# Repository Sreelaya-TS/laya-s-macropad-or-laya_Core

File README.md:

# Laya Core – 4-Key OLED Macropad 

**Honestly this was my first hardware project and this would be my 3rd edit I have added a oled that displays a cute pic**
I made this for fun and exposure to design my own pcb overall the project was fun to make and I had my good time figuring out and learning how a keyboard actualy works from yt videos, documentations and github repos etc. and for this project since I knew python already I have used kmk firmware and all the keys r directly connected to mcu 

This project includes a **custom PCB**, **KMK firmware**, and a **3D-printed case**.

---

##PARTS USED

- 4 programmable mechanical keys  
- XIAO RP2040 microcontroller  
- OLED display (I2C, 128×64)  
- KMK (CircuitPython-based) firmware  
- Custom PCB designed in KiCad  
- 3D printed enclosure (Fusion 360)
- 4 × M3 × 10 mm self-tapping screws  

---

## Firmware

- Written using **KMK firmware**
- Supports:
  - Custom keyboard shortcuts i just have added (screenshots, copy, paste, etc.)
  - OLED bitmap display (cute robot graphic)

> Firmware source code is available in this repository.

---

## 📸 Project Images

### 🟢 PCB Layout
<!-- Add your PCB image here -->

---

### 🔵 Schematic
<!-- Add your schematic image here -->

---

### 🟣 Final 3D Model (Fusion 360)
<!-- Add your Fusion 360 render here -->

---

## 🔌 OLED Display

- OLED communicates via **I2C**
- Resolution: **128 × 64**
- Displays a custom bitmap 
---

## 🧩 Bill of Materials (BOM)

---

## 🛠️ Tools Used

- **KiCad** – schematic and PCB design  
- **Fusion 360** – 3D modeling  
- **KMK Firmware** – keyboard firmware  
- **CircuitPython**  
- **Git & GitHub**
---

## 💙 Author

**Sreelaya TS**  
---

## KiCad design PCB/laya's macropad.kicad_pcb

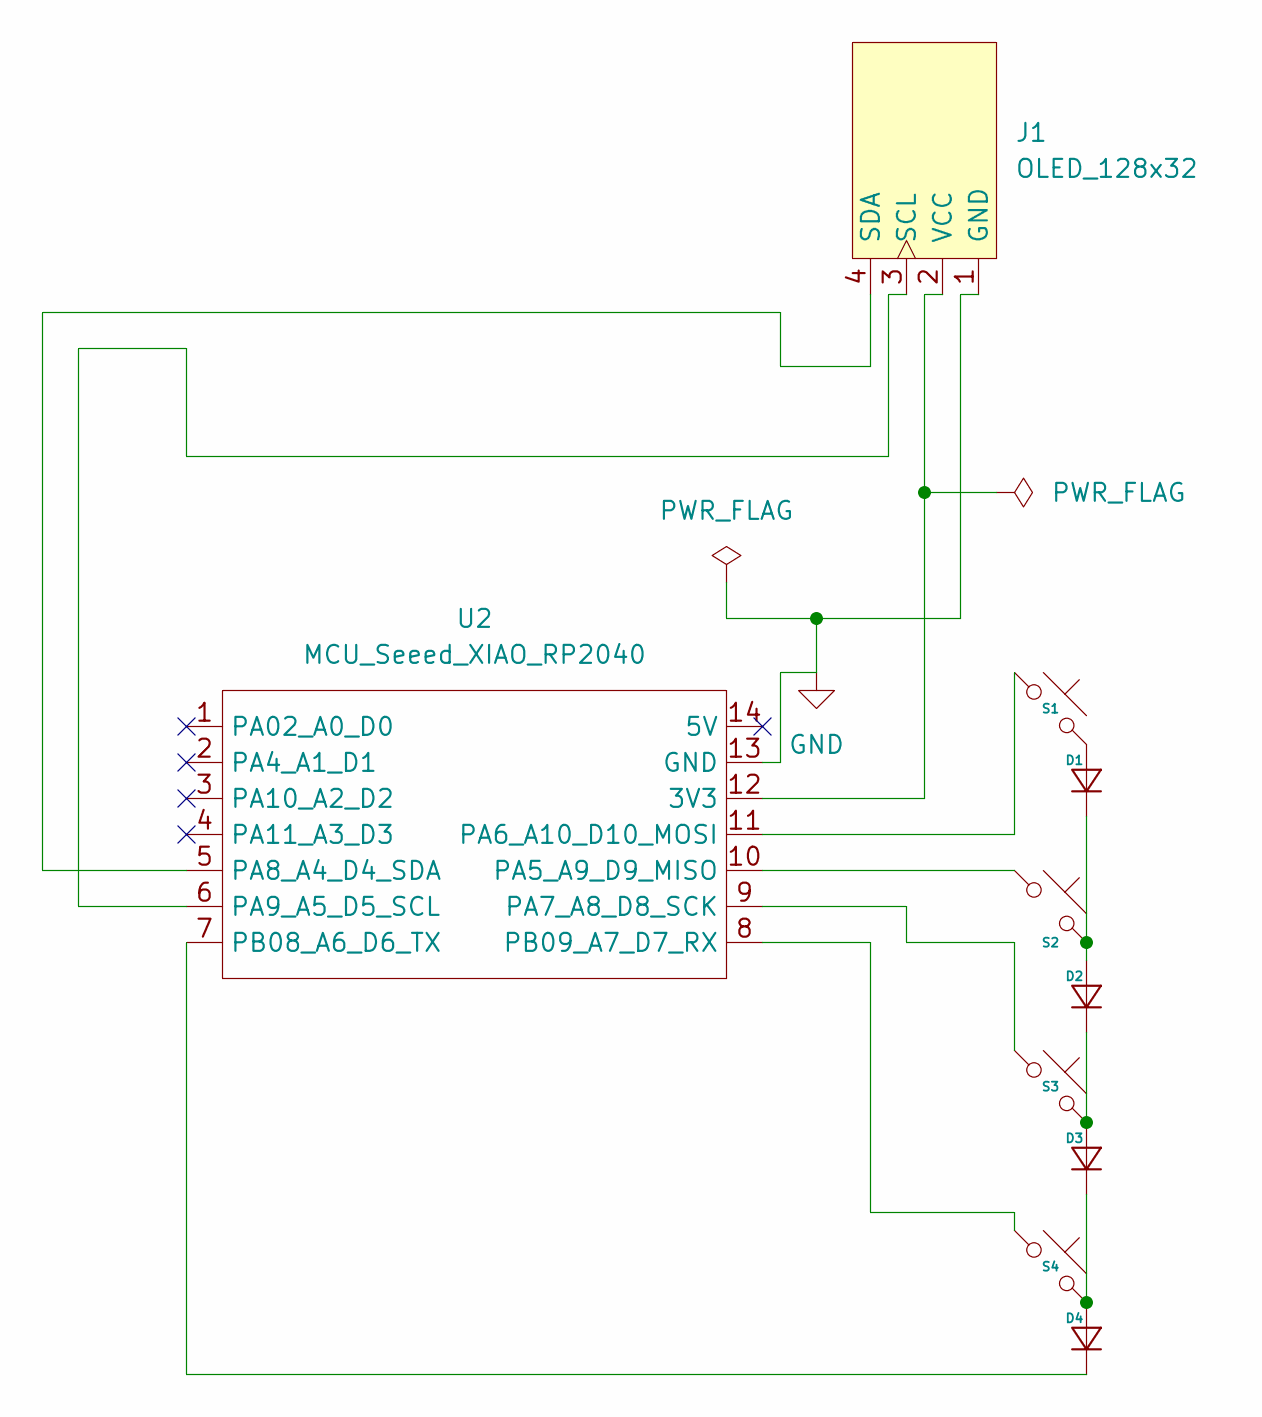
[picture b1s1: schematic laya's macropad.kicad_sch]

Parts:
D1, D2, D3, D4: Diode_DO-35
J1: OLED_128x32
S1, S2, S3, S4: MX_PCB_1.00u
U2: MCU_Seeed_XIAO_RP2040; Seeed_XIAO_RP2040

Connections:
GND: J1.1 (GND), U2.13 (GND)
unnamed: D1.2 (A), S1.2
unnamed: D1.1 (K), D2.2 (A), S2.2
unnamed: D2.1 (K), D3.2 (A), S3.2
unnamed: D3.1 (K), D4.2 (A), S4.2
unnamed: D4.1 (K), U2.7 (PB08_A6_D6_TX)
unnamed: J1.3 (SCL), U2.6 (PA9_A5_D5_SCL)
unnamed: J1.4 (SDA), U2.5 (PA8_A4_D4_SDA)
unnamed: J1.2 (VCC), U2.12 (3V3)
unnamed: S2.1, U2.10 (PA5_A9_D9_MISO)
unnamed: S1.1, U2.11 (PA6_A10_D10_MOSI)
unnamed: S3.1, U2.9 (PA7_A8_D8_SCK)
unnamed: S4.1, U2.8 (PB09_A7_D7_RX)

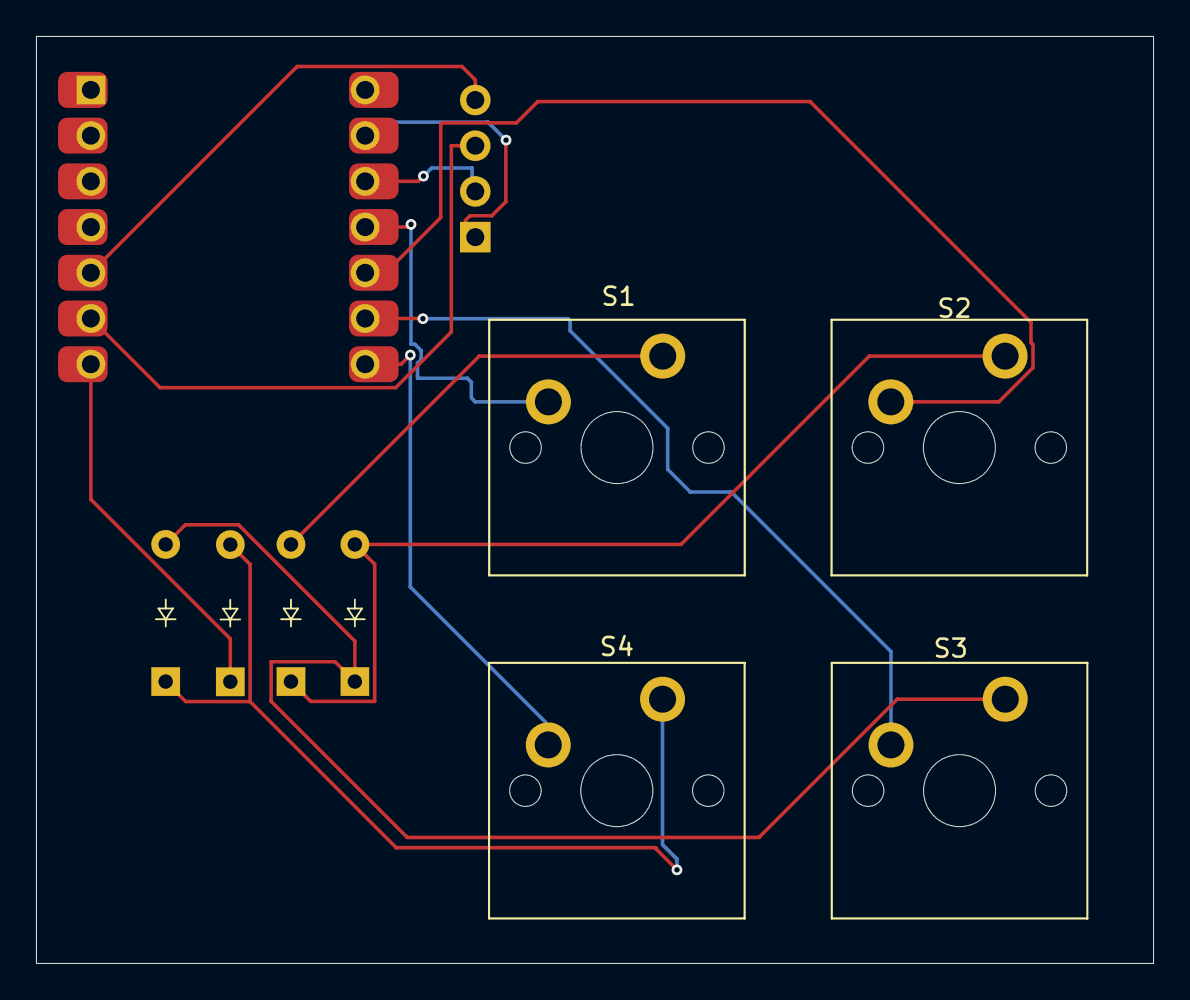
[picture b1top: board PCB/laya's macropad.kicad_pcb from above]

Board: 2 copper layers, 62.1 x 51.5 mm, 10 parts (0 on the bottom side), 13 nets.

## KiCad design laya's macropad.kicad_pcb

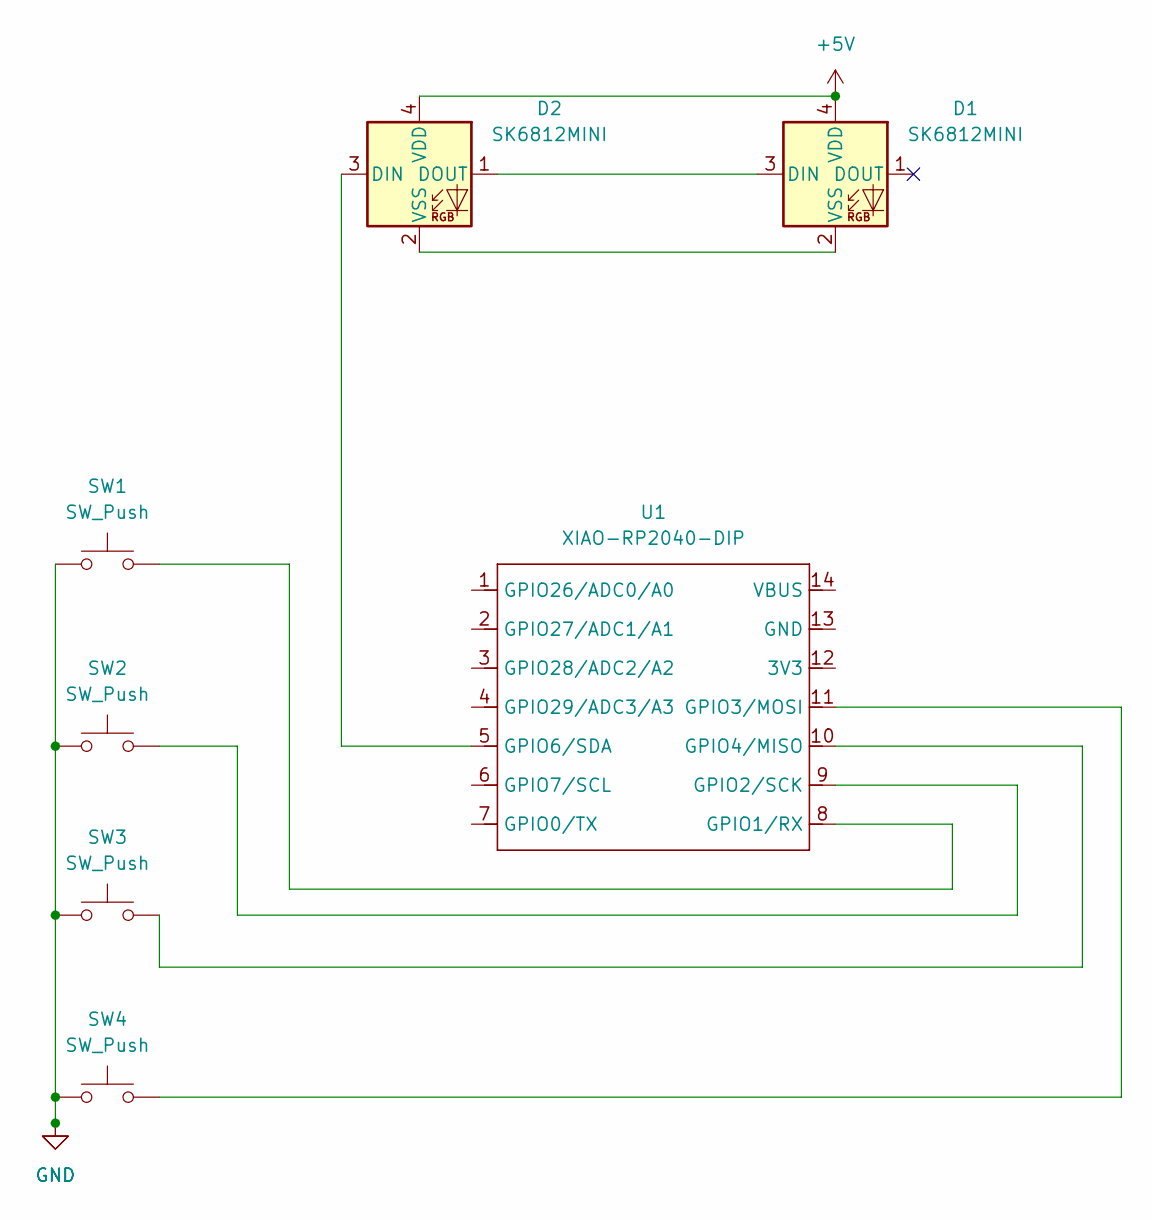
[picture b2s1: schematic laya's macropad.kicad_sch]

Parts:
D1, D2: SK6812MINI; LED_SK6812MINI_PLCC4_3.5x3.5mm_P1.75mm
SW1, SW2, SW3, SW4: SW_Push; SW_Cherry_MX_1.00u_PCB
U1: XIAO-RP2040-DIP

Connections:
+5V: D1.4 (VDD), D2.4 (VDD)
GND: SW1.1, SW2.1, SW3.1, SW4.1
unnamed: D1.3 (DIN), D2.1 (DOUT)
unnamed: D1.2 (VSS), D2.2 (VSS)
unnamed: D2.3 (DIN), U1.5 (GPIO6/SDA)
unnamed: SW1.2, U1.8 (GPIO1/RX)
unnamed: SW2.2, U1.9 (GPIO2/SCK)
unnamed: SW4.2, U1.11 (GPIO3/MOSI)
unnamed: SW3.2, U1.10 (GPIO4/MISO)

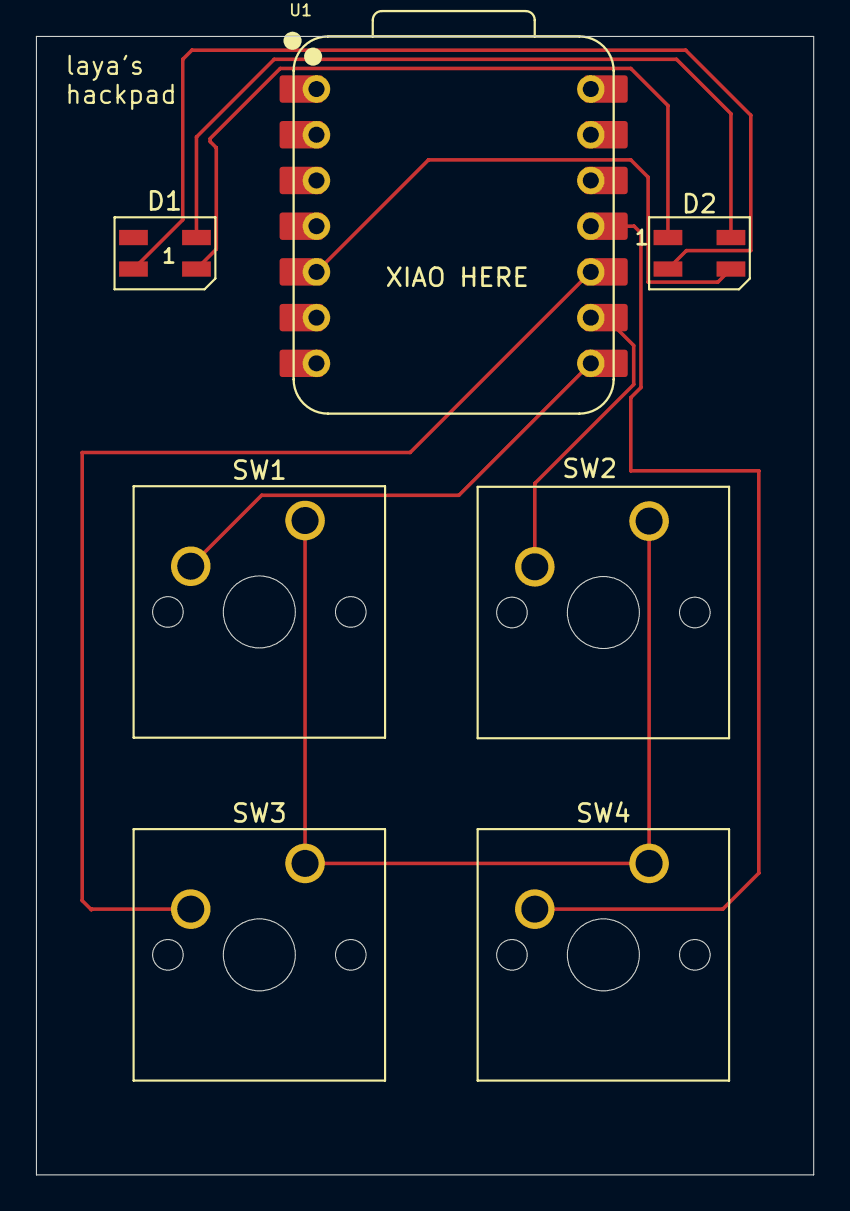
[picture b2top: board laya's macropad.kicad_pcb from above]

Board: 2 copper layers, 43.2 x 63.2 mm, 7 parts (0 on the bottom side), 9 nets.

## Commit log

2026-02-03 Add files via upload
    it is a custom macropad built to make my coding journey easier
2026-02-07 Add README for Laya Core macropad project
    Add detailed project description, features, firmware, images, BOM, tools, and future improvements for the Laya Core macropad.
2026-02-07 Added OLED robot + updated KMK firmware
2026-02-07 Revise README with project details and updates
    Updated project description, features, and parts used. Revised future improvements and author section.
2026-02-13 Updated files
2026-02-13 Updated 3d img
2026-02-13 added bom.csv
2026-02-20 oled changed
2026-02-20 3d_image added
2026-02-21 Updated PCB image and README
2026-02-21 schemantic img updated
2026-02-21 Ignore KiCad lock files
2026-02-22 schemantic
2026-02-22 Update schematic image reference in README
